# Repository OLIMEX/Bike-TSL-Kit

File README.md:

# Bike-TSL-Kit

[Bike-TSL-Kit](https://www.olimex.com/Products/Soldering-Kits/Bike-TSL-Kit/open-source-hardware) is soldering kit which adds Audi style turn signal lights to your bike.

# License
- Hardware is with CERN OHL v1.2 license
- Documentation is with CC BY-SA 4.0 license

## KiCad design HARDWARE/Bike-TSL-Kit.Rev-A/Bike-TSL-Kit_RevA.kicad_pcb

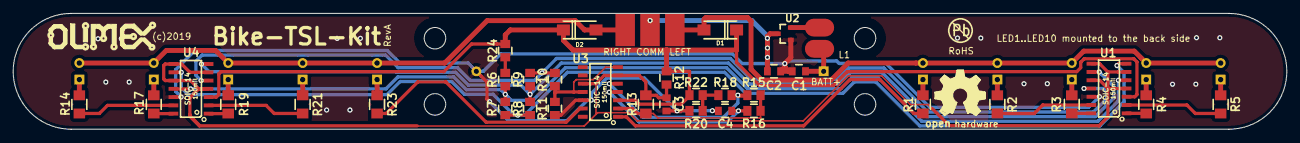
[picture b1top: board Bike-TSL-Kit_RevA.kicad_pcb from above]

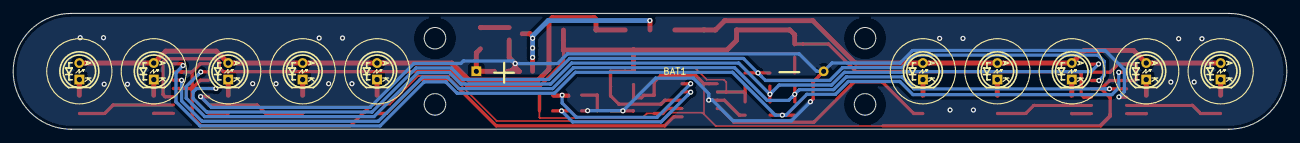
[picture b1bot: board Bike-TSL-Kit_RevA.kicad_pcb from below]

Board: 2 copper layers, 195.5 x 17.8 mm, 53 parts (11 on the bottom side), 38 nets.

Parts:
BAT1: Battery; BATTERY-1xAA
C1, C2, C3, C4: 10uF; C_0805_5MIL_DWS
D1, D2: 1N5822_SS34_SMA; SMA-KA
L1: 4.7uH; CD43
LED1, LED2, LED3, LED4, LED5, LED6, LED7, LED8, LED9, LED10: LED; LED10mmPTHKA
MountingHole*: Mounting_hole_3.3mm
MountingHole*#2, MountingHole*#3, MountingHole*#4: Mounting_hole_3.3mm
R1, R2, R3, R4, R5, R13, R14, R17, R19, R21, R23: 220R; R_1206_5MIL_DWS
R6, R7, R8, R9, R10, R11, R12, R15, R16, R18, R20, R22, R24: 22K; R_0805_5MIL_DWS
TESTPAD1, TESTPAD2, TESTPAD3: TESTPAD; TP_SMD_10.00x3.00mm
U1, U3, U4: LM339; SOIC-14_150mil
U2: BL8536; SOT23

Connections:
CAP: C3.1, R12.2, R13.2, U1.4, U1.6, U1.8, U1.10, U3.6, U3.10, U4.4, U4.6, U4.8, U4.10
GND: BAT1.2, C1.2, C2.2, C3.2, C4.1, R11.2, R20.1, U1.12, U2.1, U3.12, U4.12
LEFT: D1.2, LED6.2, LED7.2, LED8.2, LED9.2, LED10.2, TESTPAD1.1
unnamed: BAT1.1, C1.1, L1.1
unnamed: C4.2, R16.2, U3.4
unnamed: L1.2, U2.2
unnamed: LED1.1, R14.1
unnamed: LED2.1, R17.1
unnamed: LED3.1, R19.1
unnamed: LED4.1, R21.1
unnamed: LED5.1, R23.1
unnamed: LED6.1, R5.1
unnamed: LED7.1, R4.1
unnamed: LED8.1, R3.1
unnamed: LED9.1, R2.1
unnamed: LED10.1, R1.1
unnamed: R1.2, U3.1
unnamed: R2.2, U1.13
unnamed: R3.2, U1.14
unnamed: R4.2, U1.1
unnamed: R5.2, U1.2
unnamed: R6.2, R7.1, U1.5, U4.11
unnamed: R7.2, R8.1, U1.7, U4.9
unnamed: R8.2, R9.1, U1.9, U4.7
unnamed: R9.2, R10.1, U1.11, U4.5
unnamed: R10.2, R11.1, U3.7, U3.11
unnamed: R13.1, R15.1, R16.1, U3.2
unnamed: R14.2, U4.13
unnamed: R15.2, R18.1, U3.5
unnamed: R17.2, U4.14
unnamed: R18.2, R20.2, R22.2
unnamed: R19.2, U4.1
unnamed: R21.2, U4.2
unnamed: R23.2, U3.13
unnamed: R6.1, R24.2
RIGHT: D2.2, LED1.2, LED2.2, LED3.2, LED4.2, LED5.2, TESTPAD3.1
VDD: D1.1, D2.1, R12.1, R22.1, R24.1, U1.3, U3.3, U4.3
VDD_TO_LEFT_RIGHT: C2.1, TESTPAD2.1, U2.3

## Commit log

2019-10-22 initial cad files and docs
2020-04-15 new manual in French language from contributor

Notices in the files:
HARDWARE/Bike-TSL-Kit.Rev-A/Bike-TSL-Kit_RevA.kicad_pcb:
(c)2019
